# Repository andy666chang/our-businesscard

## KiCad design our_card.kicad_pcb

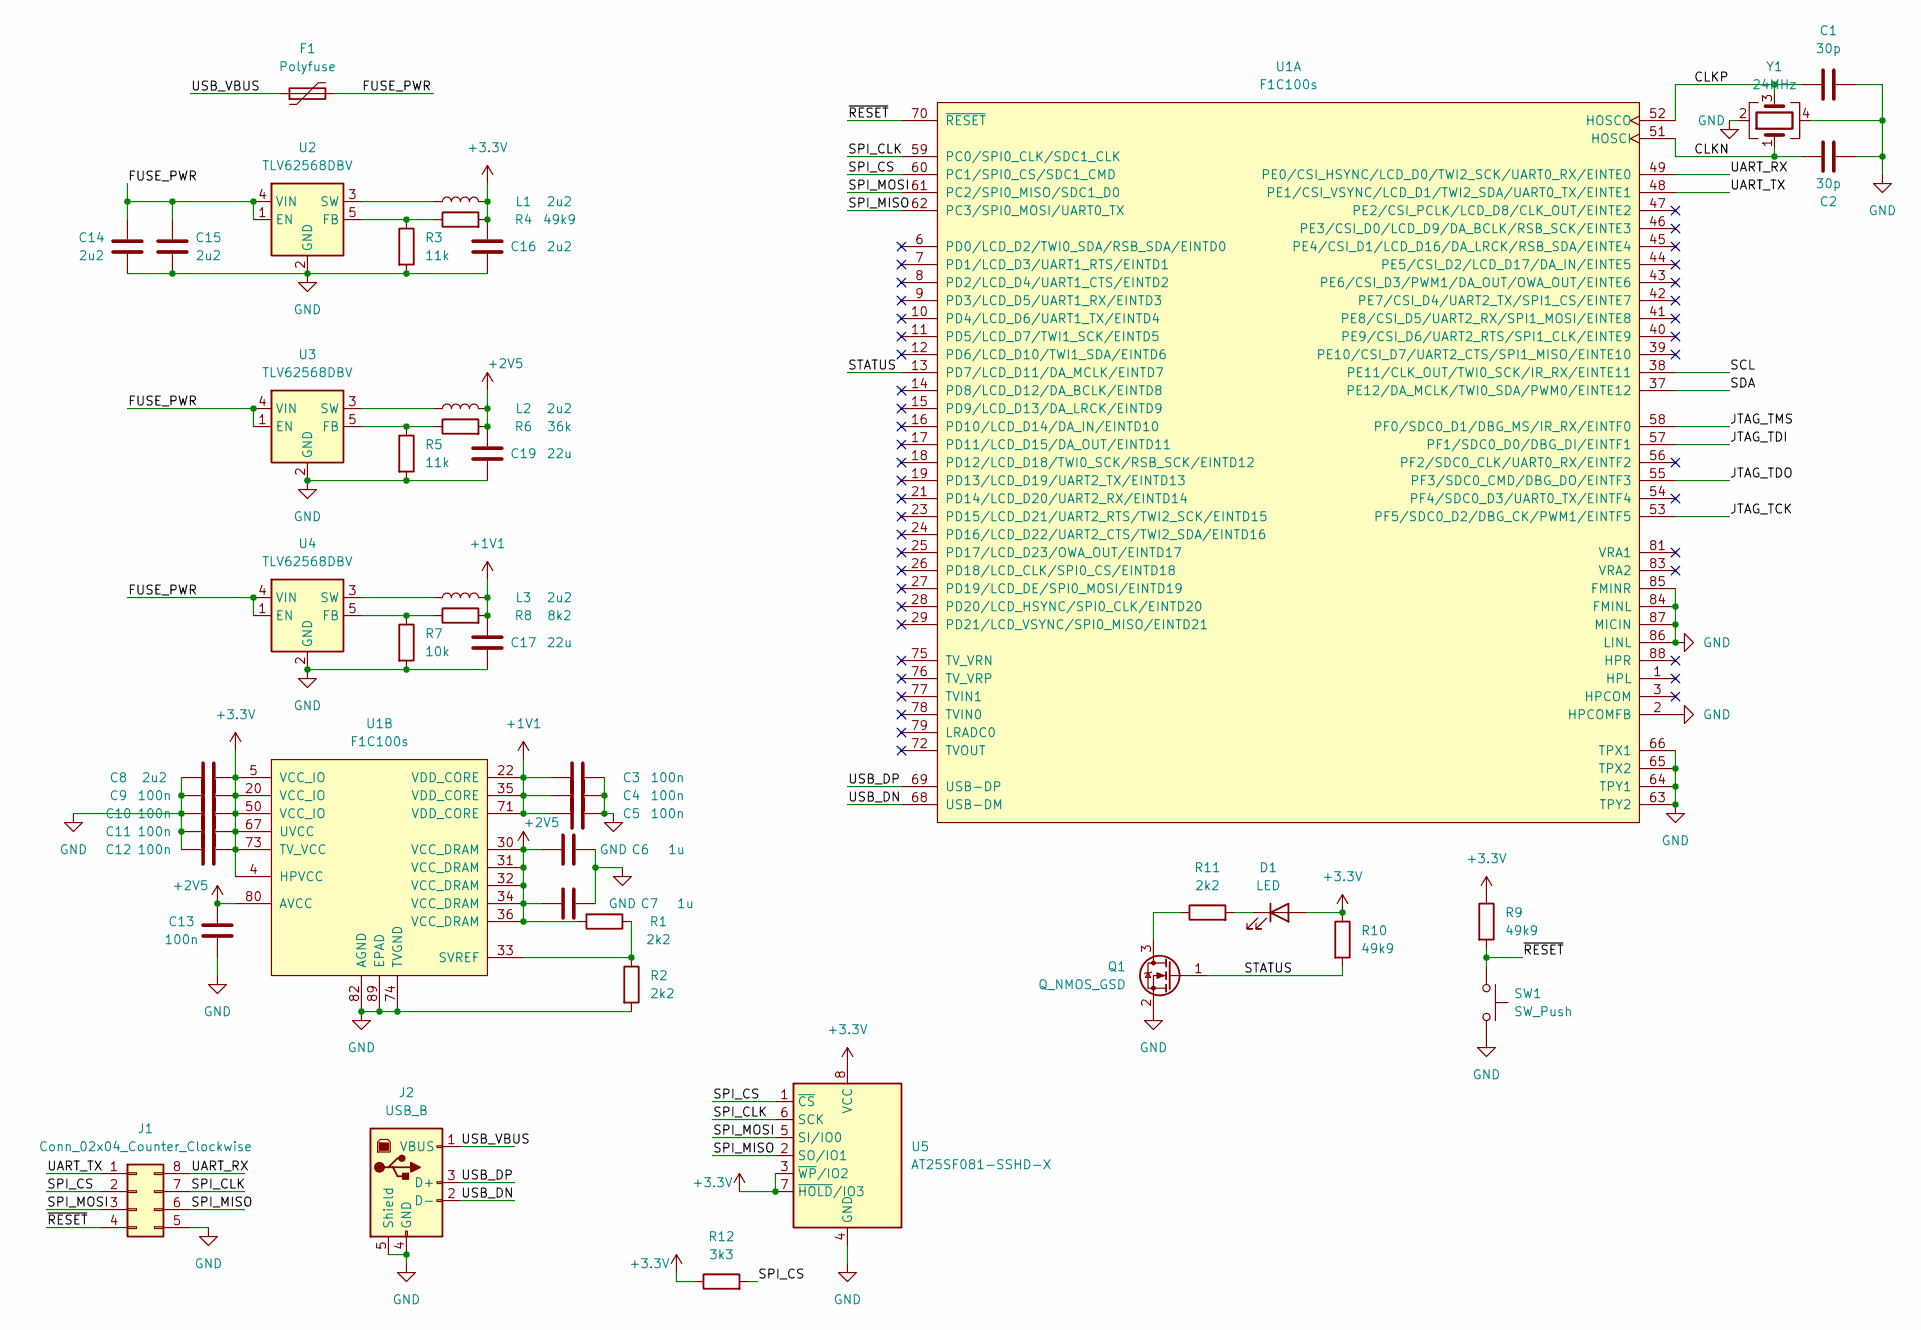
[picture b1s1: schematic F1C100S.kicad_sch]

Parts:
C1, C2: 30p; C_0603_1608Metric
C3, C4, C5, C9, C10, C11, C12, C13: 100n; C_0603_1608Metric
C6, C7: 1u; C_0603_1608Metric
C8, C14, C15, C16: 2u2; C_0603_1608Metric
C17, C19: 22u; C_0603_1608Metric
D1: LED; LED_0603_1608Metric
F1: Polyfuse; R_0603_1608Metric_Pad0.98x0.95mm_HandSolder
J1: Conn_02x04_Counter_Clockwise; PinHeader_2x04_P2.54mm_Vertical
J2: USB_B
L1, L2, L3: 2u2; L_0603_1608Metric
Q1: Q_NMOS_GSD; SOT-23-3
R1, R2, R11: 2k2; R_0603_1608Metric
R3, R5: 11k; R_0603_1608Metric
R4, R9, R10: 49k9; R_0603_1608Metric
R6: 36k; R_0603_1608Metric
R7: 10k; R_0603_1608Metric
R8: 8k2; R_0603_1608Metric
R12: 3k3; R_0603_1608Metric
SW1: SW_Push; SW_SPST_TL3342
U1: F1C100s; QFN-88_EP_10x10_Pitch0.4mm
U2, U3, U4: TLV62568DBV; SOT-23-5
U5: AT25SF081-SSHD-X; SOIC-8_3.9x4.9mm_P1.27mm
Y1: 24MHz; Oscillator_SMD_Abracon_ASE-4Pin_3.2x2.5mm

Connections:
+1V1: C3.1, C4.1, C5.1, C17.1, L3.2, R8.2, U1.22 (VDD_CORE), U1.35 (VDD_CORE), U1.71 (VDD_CORE)
+2V5: C6.1, C7.1, C13.1, C19.1, L2.2, R1.2, R6.2, U1.30 (VCC_DRAM), U1.31 (VCC_DRAM), U1.32 (VCC_DRAM), U1.34 (VCC_DRAM), U1.36 (VCC_DRAM), U1.80 (AVCC)
+3.3V: C8.1, C9.1, C10.1, C11.1, C12.1, C16.1, D1.2 (A), L1.2, R4.2, R9.1, R10.1, R12.1, U1.4 (HPVCC), U1.5 (VCC_IO), U1.20 (VCC_IO), U1.50 (VCC_IO), U1.67 (UVCC), U1.73 (TV_VCC), U5.3 (~WP/IO2), U5.7 (~HOLD/IO3), U5.8 (VCC)
/F1C100s/CLKN: C2.1, U1.51 (HOSCI), Y1.1
/F1C100s/CLKP: C1.1, U1.52 (HOSCO), Y1.3
/F1C100s/FUSE_PWR: C14.1, C15.1, F1.2, U2.1 (EN), U2.4 (VIN), U3.1 (EN), U3.4 (VIN), U4.1 (EN), U4.4 (VIN)
/F1C100s/JTAG_TCK: U1.53 (PF5/SDC0_D2/DBG_CK/PWM1/EINTF5)
/F1C100s/JTAG_TDI: U1.57 (PF1/SDC0_D0/DBG_DI/EINTF1)
/F1C100s/JTAG_TDO: U1.55 (PF3/SDC0_CMD/DBG_DO/EINTF3)
/F1C100s/JTAG_TMS: U1.58 (PF0/SDC0_D1/DBG_MS/IR_RX/EINTF0)
/F1C100s/SCL: U1.38 (PE11/CLK_OUT/TWI0_SCK/IR_RX/EINTE11)
/F1C100s/SDA: U1.37 (PE12/DA_MCLK/TWI0_SDA/PWM0/EINTE12)
/F1C100s/SPI_CLK: J1.7, U1.59 (PC0/SPI0_CLK/SDC1_CLK), U5.6 (SCK)
/F1C100s/SPI_CS: J1.2, R12.2, U1.60 (PC1/SPI0_CS/SDC1_CMD), U5.1 (~CS)
/F1C100s/SPI_MISO: J1.6, U1.62 (PC3/SPI0_MOSI/UART0_TX), U5.2 (SO/IO1)
/F1C100s/SPI_MOSI: J1.3, U1.61 (PC2/SPI0_MISO/SDC1_D0), U5.5 (SI/IO0)
/F1C100s/STATUS: Q1.1 (G), R10.2, U1.13 (PD7/LCD_D11/DA_MCLK/EINTD7)
/F1C100s/UART_RX: J1.8, U1.49 (PE0/CSI_HSYNC/LCD_D0/TWI2_SCK/UART0_RX/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)
/F1C100s/UART_TX: J1.1, U1.48 (PE1/CSI_VSYNC/LCD_D1/TWI2_SDA/UART0_TX/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)
/F1C100s/USB_DN: J2.2 (D-), U1.68 (USB-DM)
/F1C100s/USB_DP: J2.3 (D+), U1.69 (USB-DP)
/F1C100s/USB_VBUS: F1.1, J2.1 (VBUS)
/F1C100s/~RESET: J1.4, R9.2, SW1.1, U1.70 (~RESET)
GND: C1.2, C2.2, C3.2, C4.2, C5.2, C6.2, C7.2, C8.2, C9.2, C10.2, C11.2, C12.2, C13.2, C14.2, C15.2, C16.2, C17.2, C19.2, J1.5, J2.4 (GND), J2.5 (Shield), Q1.2 (S), R2.2, R3.2, R5.2, R7.2, SW1.2, U1.2 (HPCOMFB), U1.63 (TPY2), U1.64 (TPY1), U1.65 (TPX2), U1.66 (TPX1), U1.74 (TVGND), U1.82 (AGND), U1.84 (FMINL), U1.85 (FMINR), U1.86 (LINL), U1.87 (MICIN), U1.89 (EPAD), U2.2 (GND), U3.2 (GND), U4.2 (GND), U5.4 (GND), Y1.2, Y1.4
unnamed: D1.1 (K), R11.2
unnamed: Q1.3 (D), R11.1
unnamed: R1.1, R2.1, U1.33 (SVREF)
unnamed: R3.1, R4.1, U2.5 (FB)
unnamed: L1.1, U2.3 (SW)
unnamed: R5.1, R6.1, U3.5 (FB)
unnamed: L2.1, U3.3 (SW)
unnamed: R7.1, R8.1, U4.5 (FB)
unnamed: L3.1, U4.3 (SW)

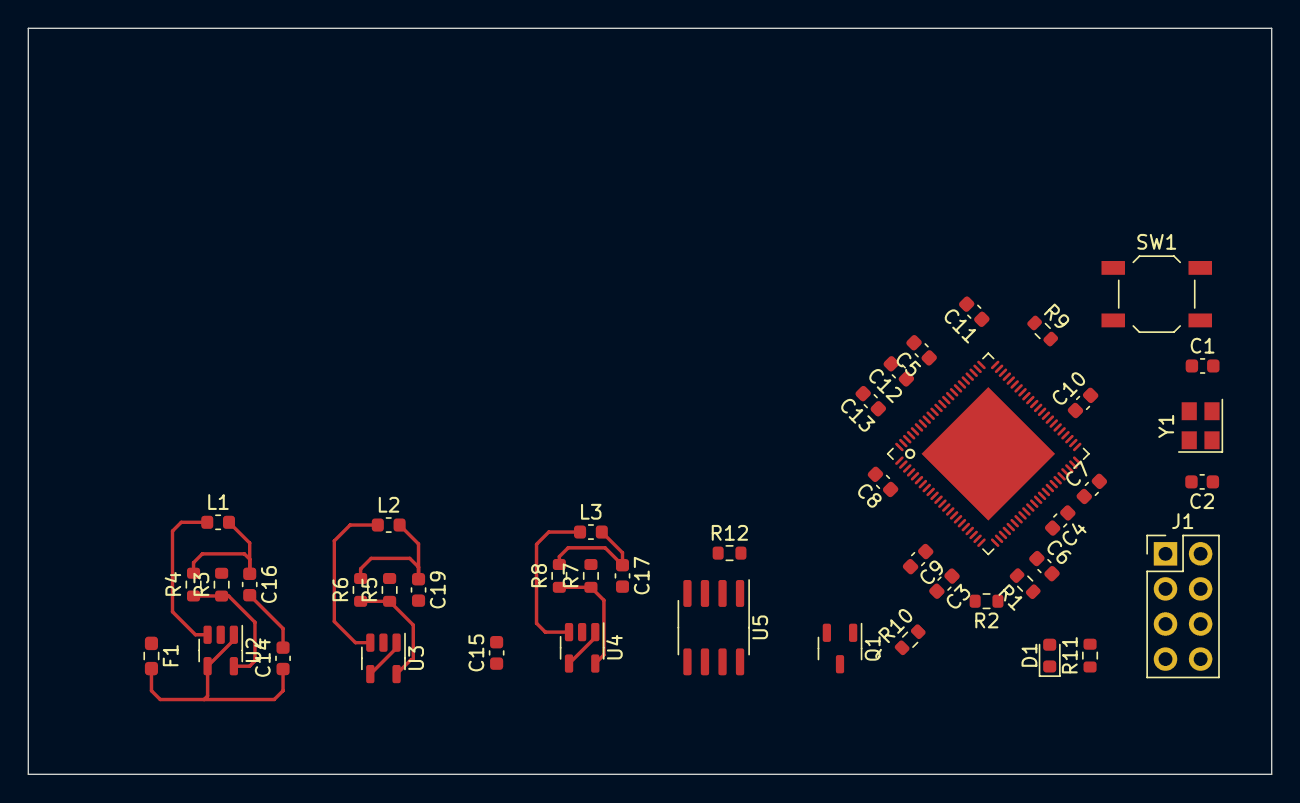
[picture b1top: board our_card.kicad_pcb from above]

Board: 2 copper layers, 90.0 x 54.0 mm, 44 parts (0 on the bottom side), 24 nets.

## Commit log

2023-08-23 fix: modify repo source
2023-08-23 feat: create basic schematic
2023-08-24 feat: replace JW5211 to TLV62568DBV
2023-08-24 fix: clone kicad library for footprint https://github.com/thirtythreeforty/3340_kicad
2023-08-25 fix: led 3v3
2023-08-26 feat: update footprint
2023-09-06 feat: update placement
